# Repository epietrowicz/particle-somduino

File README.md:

# Somduino
This is a sample design for a _mostly_ assembled PCB from a manufacturing service like JLCPCB, helping you get started with a custom SoM based design. The Somduino is an Arduino Uno form factor breakout board intended to work with either BSoM or MSoM Particle products.

## Overview
The SoMduino has the following features:
- USB Type C connector for programming
    - This development board cannot be powered via USB and will require either a LiPo battery or a DC barrel jack connection.
- ON / OFF switch
- Mode & Reset switches
- RGB LED indicator
- 5-17V DC barrel jack connector for battery charging and normal operation
- Qwiic connector for I2C expansion
- Charging indicator LED
- Arduino Uno form factor for Arduino shield compatibility

## BOM
You can find a complete list of LCSC parts used in the example design below:

| Designator | Quantity | Comment | LCSC Part # |
| --- | --- | --- | --- |
| D1 | 1 | LED RGB | C5342281 |
| D2 | 1 | LED Charging | C2297 |
| H1 | 1 | Threaded standoff | C2916321 |
| J1, J4 | 2 | 1x08 Header | C27438 |
| J2 | 1 | 1x10 Header | C5116489 |
| J3 | 1 | 1x06 Header | C40877 |
| J5 | 1 | Barrel Jack Power In | C720557 |
| J6 | 1 | 1x02 Battery connector | C295747 |
| J7 | 1 | 1x04 Qwiic connector | C160390 |
| J8 | 1 | USB-C connector | C5362630 |
| R1, R2, R3, R5 | 4 | 1k 0603 resistor | C21190 |
| R10, R9 | 2 | 5.1k 0603 resistor | C23186 |
| R4, R8 | 2 | 10k 0603 resistor | C15401 |
| R6, R7 | 2 | 4.7k 0603 resistor | C23162 |
| SW1, SW2 | 2 | Push button switch | C318884 |
| SW3 | 1 | Power switch | C963205 |
| U1 | 1 | M.2 connector for SoM | C2977809 |

The cost of the example design is $54.88 for 5 mostly assembled boards. All that remains is a Particle SoM and power module. It is worth noting that I did not choose to upgrade from the “economic assembly” for the threaded standoff and plan to hand assemble that component saving $25.

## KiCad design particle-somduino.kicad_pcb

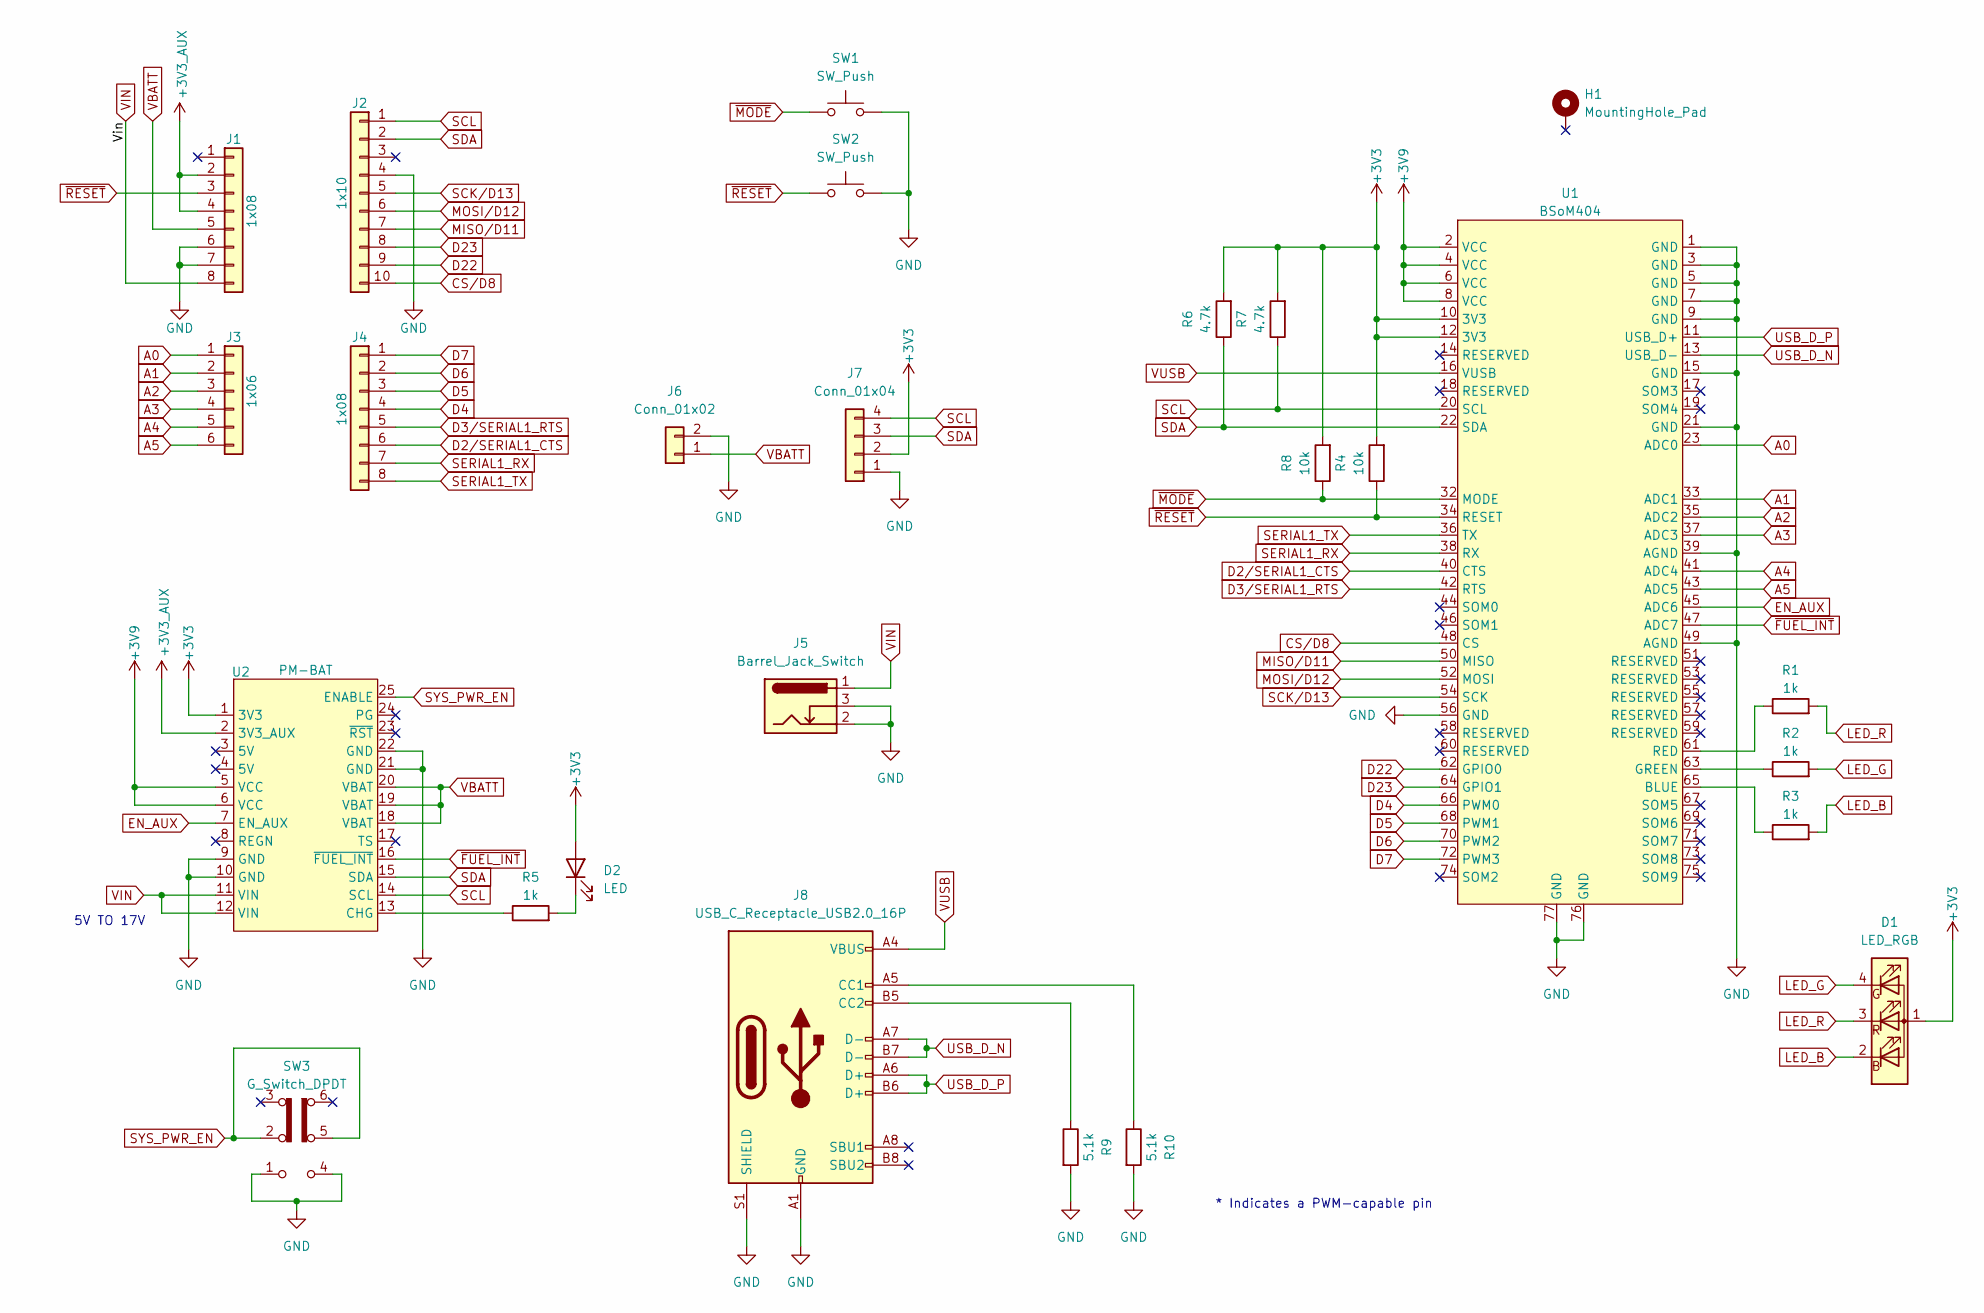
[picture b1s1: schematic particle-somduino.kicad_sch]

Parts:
D1: LED_RGB; LED_RGB_Wuerth-PLCC4_3.2x2.8mm_150141M173100; LCSC C5342281
D2: LED; LED_0805_2012Metric; LCSC C2297
H1: MountingHole_Pad; SoM_SMD_ThreadedStandoff; LCSC C2916321
J1, J4: 1x08; PinSocket_1x08_P2.54mm_Vertical; LCSC C27438
J2: 1x10; PinSocket_1x10_P2.54mm_Vertical; LCSC C5116489
J3: 1x06; PinSocket_1x06_P2.54mm_Vertical; LCSC C40877
J5: Barrel_Jack_Switch; DC-005-A200; LCSC C720557
J6: Conn_01x02; JST_PH_S2B-PH-SM4-TB_1x02-1MP_P2.00mm_Horizontal; LCSC C295747
J7: Conn_01x04; JST_SH_BM04B-SRSS-TB_1x04-1MP_P1.00mm_Vertical; LCSC C160390
J8: USB_C_Receptacle_USB2.0_16P; USB_C_Receptacle_G-Switch_GT-USB-7010i; LCSC C5362630
R1, R2, R3, R5: 1k; R_0603_1608Metric; LCSC C21190
R4, R8: 10k; R_0603_1608Metric; LCSC C15401
R6, R7: 4.7k; R_0603_1608Metric; LCSC C23162
R9, R10: 5.1k; R_0603_1608Metric; LCSC C23186
SW1, SW2: SW_Push; SW_Push_1P1T_XKB_TS-1187A; LCSC C318884
SW3: G_Switch_DPDT; G-Swtich_SW_DPDT; LCSC C963205
U1: BSoM404; SoM_M2_Connector; LCSC C2977809
U2: PM-BAT; ParticlePowerModuleSMD

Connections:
+3V3: D1.1 (A), D2.2 (A), J7.2, R4.2, R6.2, R7.2, R8.2, U1.10 (3V3), U1.12 (3V3), U2.1 (3V3)
+3V3_AUX: J1.2, J1.4, U2.2 (3V3_AUX)
+3V9: U1.2 (VCC), U1.4 (VCC), U1.6 (VCC), U1.8 (VCC), U2.5 (VCC), U2.6 (VCC)
A0: J3.1, U1.23 (ADC0)
A1: J3.2, U1.33 (ADC1)
A2: J3.3, U1.35 (ADC2)
A3: J3.4, U1.37 (ADC3)
A4: J3.5, U1.41 (ADC4)
A5: J3.6, U1.43 (ADC5)
CS/D8: J2.10, U1.48 (CS)
D2/SERIAL1_CTS: J4.6, U1.40 (CTS)
D3/SERIAL1_RTS: J4.5, U1.42 (RTS)
D4: J4.4, U1.66 (PWM0)
D5: J4.3, U1.68 (PWM1)
D6: J4.2, U1.70 (PWM2)
D7: J4.1, U1.72 (PWM3)
D22: J2.9, U1.62 (GPIO0)
D23: J2.8, U1.64 (GPIO1)
EN_AUX: U1.45 (ADC6), U2.7 (EN_AUX)
GND: J1.6, J1.7, J2.4, J5.2, J5.3, J6.2, J7.1, J8.A1 (GND), J8.A12 (GND), J8.B1 (GND), J8.B12 (GND), J8.S1 (SHIELD), R9.2, R10.2, SW1.2, SW2.2, SW3.1 (C), SW3.4 (A), U1.1 (GND), U1.3 (GND), U1.5 (GND), U1.7 (GND), U1.9 (GND), U1.15 (GND), U1.21 (GND), U1.39 (AGND), U1.49 (AGND), U1.56 (GND), U1.76 (GND), U1.77 (GND), U2.9 (GND), U2.10 (GND), U2.21 (GND), U2.22 (GND)
LED_B: D1.2 (BK), R3.2
LED_G: D1.4 (RK), R2.2
LED_R: D1.3 (GK), R1.2
MISO/D11: J2.7, U1.50 (MISO)
MOSI/D12: J2.6, U1.52 (MOSI)
unnamed: D2.1 (K), R5.2
unnamed: J8.A5 (CC1), R10.1
unnamed: J8.B5 (CC2), R9.1
unnamed: R3.1, U1.65 (BLUE)
unnamed: R2.1, U1.63 (GREEN)
unnamed: R1.1, U1.61 (RED)
unnamed: R5.1, U2.13 (CHG)
SCK/D13: J2.5, U1.54 (SCK)
SCL: J2.1, J7.4, R7.1, U1.20 (SCL), U2.14 (SCL)
SDA: J2.2, J7.3, R6.1, U1.22 (SDA), U2.15 (SDA)
SERIAL1_RX: J4.7, U1.38 (RX)
SERIAL1_TX: J4.8, U1.36 (TX)
SYS_PWR_EN: SW3.2 (B), SW3.5 (B), U2.25 (ENABLE)
USB_D_N: J8.A7 (D-), J8.B7 (D-), U1.13 (USB_D-)
USB_D_P: J8.A6 (D+), J8.B6 (D+), U1.11 (USB_D+)
VBATT: J1.5, J6.1, U2.18 (VBAT), U2.19 (VBAT), U2.20 (VBAT)
VIN: J1.8, J5.1, U2.11 (VIN), U2.12 (VIN)
VUSB: J8.A4 (VBUS), J8.A9 (VBUS), J8.B4 (VBUS), J8.B9 (VBUS), U1.16 (VUSB)
~FUEL_INT: U1.47 (ADC7), U2.16 (~FUEL_INT)
~MODE: R8.1, SW1.1, U1.32 (MODE)
~RESET: J1.3, R4.1, SW2.1, U1.34 (RESET)

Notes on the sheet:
5V TO 17V
* Indicates a PWM-capable pin

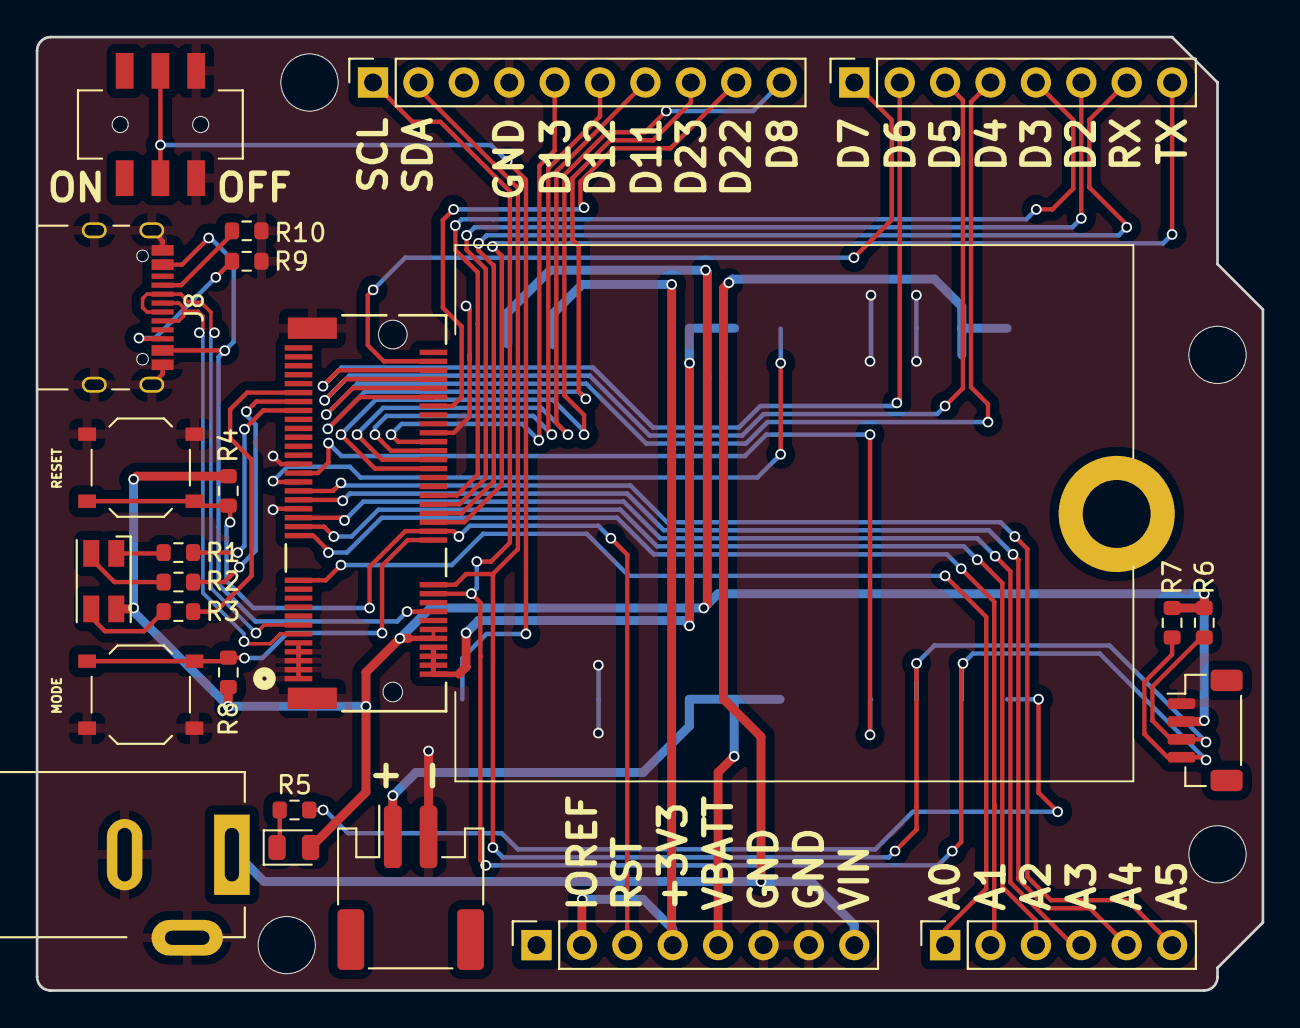
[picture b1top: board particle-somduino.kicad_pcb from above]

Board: 2 copper layers, 68.6 x 53.3 mm, 30 parts (1 on the bottom side), 46 nets.

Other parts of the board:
MH1, MH2, MH3, MH4: MountingHole_3.2mm

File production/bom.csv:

Designator,Footprint,Quantity,Value,LCSC Part #
D1,LED_RGB_Wuerth-PLCC4_3.2x2.8mm_150141M173100,1,LED_RGB,C5342281
D2,0805,1,LED,C2297
H1,SoM_SMD_ThreadedStandoff,1,MountingHole_Pad,C2916321
"J1, J4",PinSocket_1x08_P2.54mm_Vertical,2,1x08,C27438
J2,PinSocket_1x10_P2.54mm_Vertical,1,1x10,C5116489
J3,PinSocket_1x06_P2.54mm_Vertical,1,1x06,C40877
J5,DC-005-A200,1,Barrel_Jack_Switch,C720557
J6,JST_PH_S2B-PH-SM4-TB_1x02-1MP_P2.00mm_Horizontal,1,Conn_01x02,C295747
J7,JST_SH_BM04B-SRSS-TB_1x04-1MP_P1.00mm_Vertical,1,Conn_01x04,C160390
J8,USB_C_Receptacle_G-Switch_GT-USB-7010i,1,USB_C_Receptacle_USB2.0_16P,C5362630
"R1, R2, R3, R5",0603,4,1k,C21190
"R10, R9",0603,2,5.1k,C23186
"R4, R8",0603,2,10k,C15401
"R6, R7",0603,2,4.7k,C23162
"SW1, SW2",SW_Push_1P1T_XKB_TS-1187A,2,SW_Push,C318884
SW3,G-Swtich_SW_DPDT,1,G_Switch_DPDT,C963205
U1,SoM_M2_Connector,1,BSoM404,C2977809
U2,ParticlePowerModuleSMD,1,PM-BAT,

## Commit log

2024-12-04 gitignore
2024-12-05 include bom files
2024-12-05 reset gitignore
2025-02-05 tweaks
